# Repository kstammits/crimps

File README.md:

# crimps
 Mutated Kinks = Karltron Crimps

Originally cloning Mutable Instruments' Kinks
https://github.com/pichenettes/eurorack
Transferring from EAGLE to KiCad and updating from 0402 to 0805 construction means basically the whole thing is rewritten from scratch. The PCB is therefore unrelated to Kinks: Crimps is a karltron design 2021. 

Info on karltron.com/crimps

it's cc-by-sa so copyleft

On the internet forums, someone else has mentioned started a THT version, asking about it but not shared yet because reasons. 
https://modwiggler.com/forum/viewtopic.php?p=3644155

signal diode:
FDLL4148 is D1206

changing pinout on transistors, to SOT-23. so DO BE CAREFUL AND RECHECK THE PINOUT  (note v101 has the transistors on upside down)

layout looking fine in 0805

The S&H calls for a fancy C0G capacitor and OPA4171 opamp. We'll try it with a plain capacitor and TL074, which are compatible, but expect poor performance. I'm curious how poor, if it's acceptable we can save $$. Will try both, and report back here. But v101 is otherwise broken so 

when the input looks like noise at >9vpp, which is normal, the trigger goes off for successivly lower notes. feels like an accumulating towards -7.5Volts. Input values lower than -7V till self trigger If something softer is in the input, or values <7 volts absolute it will not self-trigger.  i think i need to add a capacitor somewhere or redo the ground plane.  Anytime the input sinks below -7V it pulls on the gate. Not sure it's really triggering, would need a two-channel scope to see if they coincide.  

if you keep the input above -7V, then the vgs doesn't trigger and everything is good. So I should just reduce the noise volume, the original kinks was showing just about +/-5V, and 10vpp is enough noise. mine's doing like 19vpp noise, and catching a very brief acquisition during noise spikes under -7V. 

so actually it works fine. i should/need/to/ reduce the noise volume to 10vpp to avoid the -7V issue. That's fixed by changing R27 from a 1.5M as originally given to a 1M. Now the noise is only +/-6V and everything works. then of course flip the transistors right-side-up. I've tested with only a J112 THT jfet tacked on crooked.  

Testing another JFET as replacement; the MMBFJ201 (marked 6P) is not great. Sort of works, sort of doesnt. The trigger time is not sufficient for acquisition, so each trigger can only move the sample by a few volts, and swinging +/-10V will need 2,3,4,5 triggers. Also, when the input is quite low the sample drains without triggers, so the J201 seems to have some leakage Igs as well as a higher Rds-on vs the J112. The incomplete-acquisitions problem might be okay for your use, but it really reduces the output range when the internal noise source is +/-6V and each trigger seems to only change the value to +/-1V. 

Testing the MMBF4392 (marked 6K)
Holds nicely down to -7.5V then drops, as others do, because my gate off voltage is -11, so less than four difference causes a sampling.   Seems to be working well. 

Testing the MMBFJ112 (marked 6R) last since a THT J112 was working well. Also seems to perform adequately. 
 
During hold testing, discovered unplugging and replugging the output causes a drop in the sample; perhaps this is caused by the brief short to ground pulling on the opamp. Additional decoupling caps did not help, looks like the OPA4171 final out buffer loses some state through the 180R output. Another output stage might be required to separate the held voltage from the output buffer. That's not fixable without additional chips.

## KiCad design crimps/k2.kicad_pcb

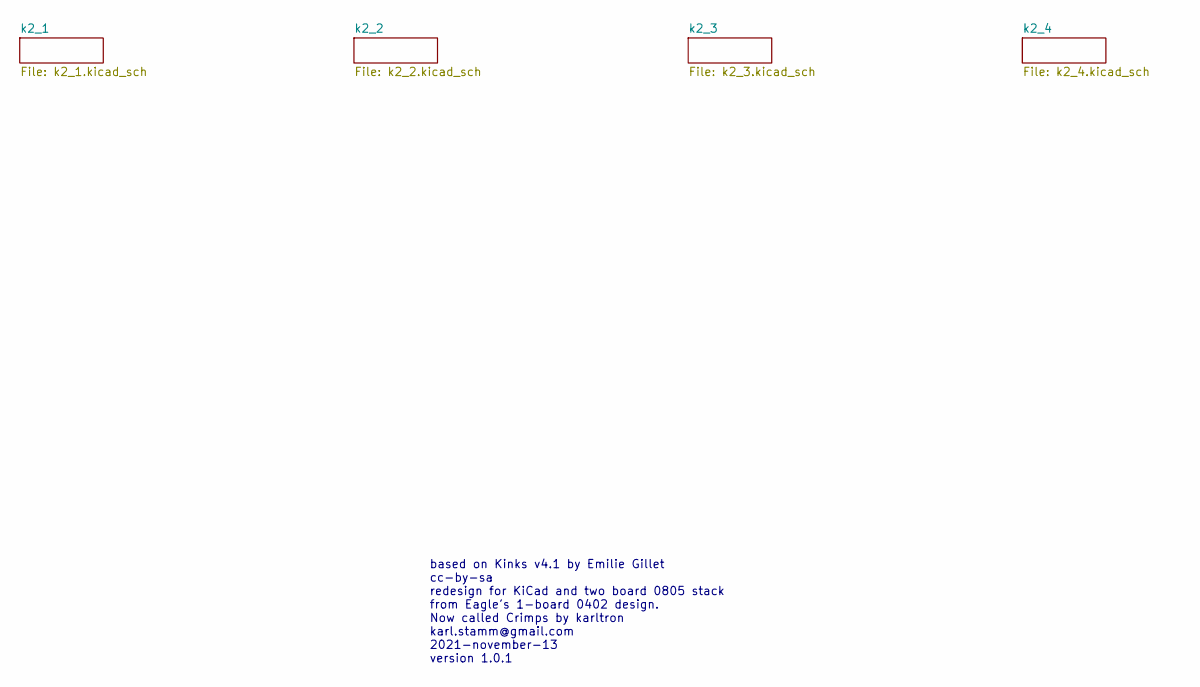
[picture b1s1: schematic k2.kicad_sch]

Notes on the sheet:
based on Kinks v4.1 by Emilie Gillet cc-by-sa redesign for KiCad and two board 0805 stack from Eagle's 1-board 0402 design. Now called Crimps by karltron karl.stamm@gmail.com 2021-november-13 version 1.0.1

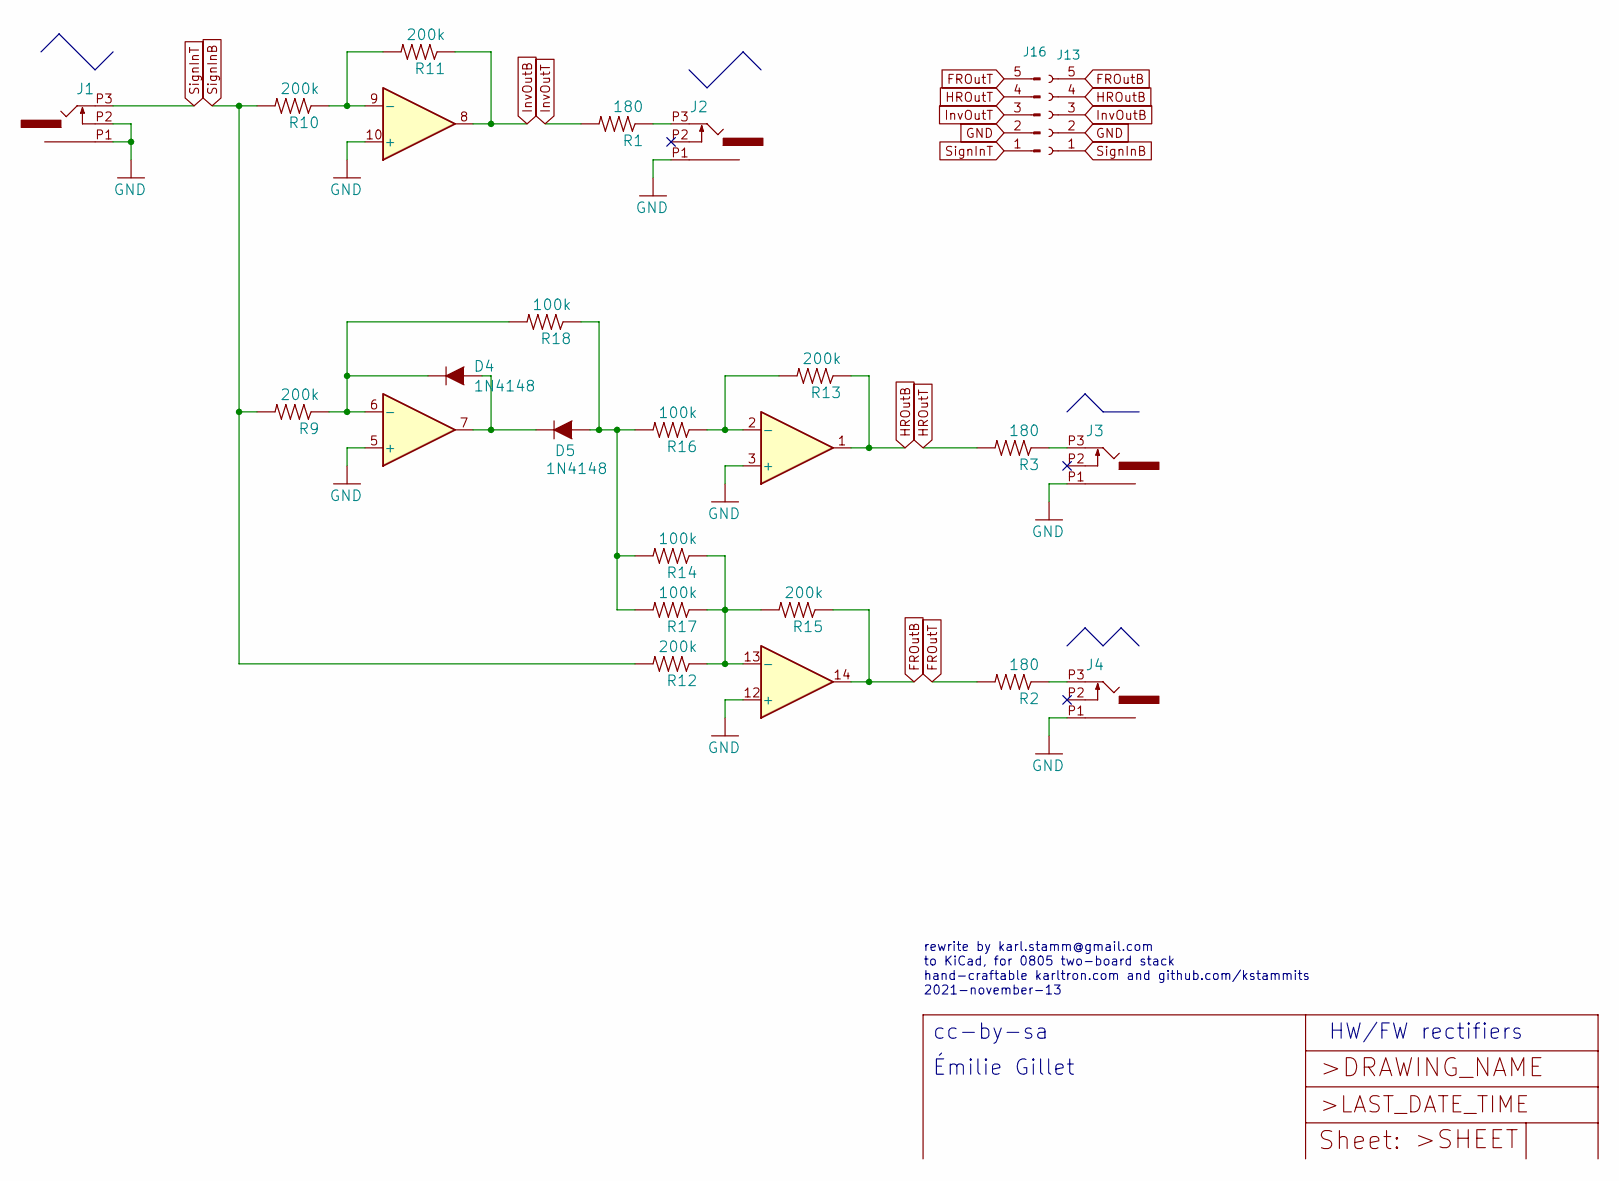
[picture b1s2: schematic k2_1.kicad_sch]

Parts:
D4, D5: 1N4148; D_1206_3216Metric_Pad1.42x1.75mm_HandSolder
IC1: TL074; SOIC-14_3.9x8.7mm_P1.27mm
J1, J2, J3, J4: PJ301_THONKICONN6; WQP_PJ_301M6
J13: Conn_01x05_Female; PinHeader_1x05_P2.54mm_Vertical
J16: Conn_01x05_Male; PinHeader_1x05_P2.54mm_Vertical
R1, R2, R3: 180; R_0805_2012Metric_Pad1.20x1.40mm_HandSolder
R9, R10, R11, R12, R13, R15: 200k; R_0805_2012Metric_Pad1.20x1.40mm_HandSolder
R14, R16, R17, R18: 100k; R_0805_2012Metric_Pad1.20x1.40mm_HandSolder

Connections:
FROutB: IC1.14, J13.5, R15.1
FROutT: J16.5, R2.2
GND: IC1.3 (+), IC1.5 (+), IC1.10 (+), IC1.12 (+), J1.P1 (1), J1.P2 (2), J2.P1 (1), J3.P1 (1), J4.P1 (1), J13.2, J16.2; also elsewhere on the board
HROutB: IC1.1, J13.4, R13.1
HROutT: J16.4, R3.2
InvOutB: IC1.8, J13.3, R11.1
InvOutT: J16.3, R1.2
unnamed: D4.2 (A), D5.1 (K), IC1.7
unnamed: D4.1 (K), IC1.6 (-), R9.1, R18.2
unnamed: D5.2 (A), R14.2, R16.2, R17.2, R18.1
unnamed: IC1.2 (-), R13.2, R16.1
unnamed: IC1.9 (-), R10.1, R11.2
unnamed: IC1.13 (-), R12.1, R14.1, R15.2, R17.1
unnamed: J2.P3 (3), R1.1
unnamed: J3.P3 (3), R3.1
unnamed: J4.P3 (3), R2.1
SignInB: J13.1, R9.2, R10.2, R12.2
SignInT: J1.P3 (3), J16.1

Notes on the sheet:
Émilie Gillet
HW/FW rectifiers
rewrite by karl.stamm@gmail.com to KiCad, for 0805 two-board stack hand-craftable karltron.com and github.com/kstammits 2021-november-13
cc-by-sa

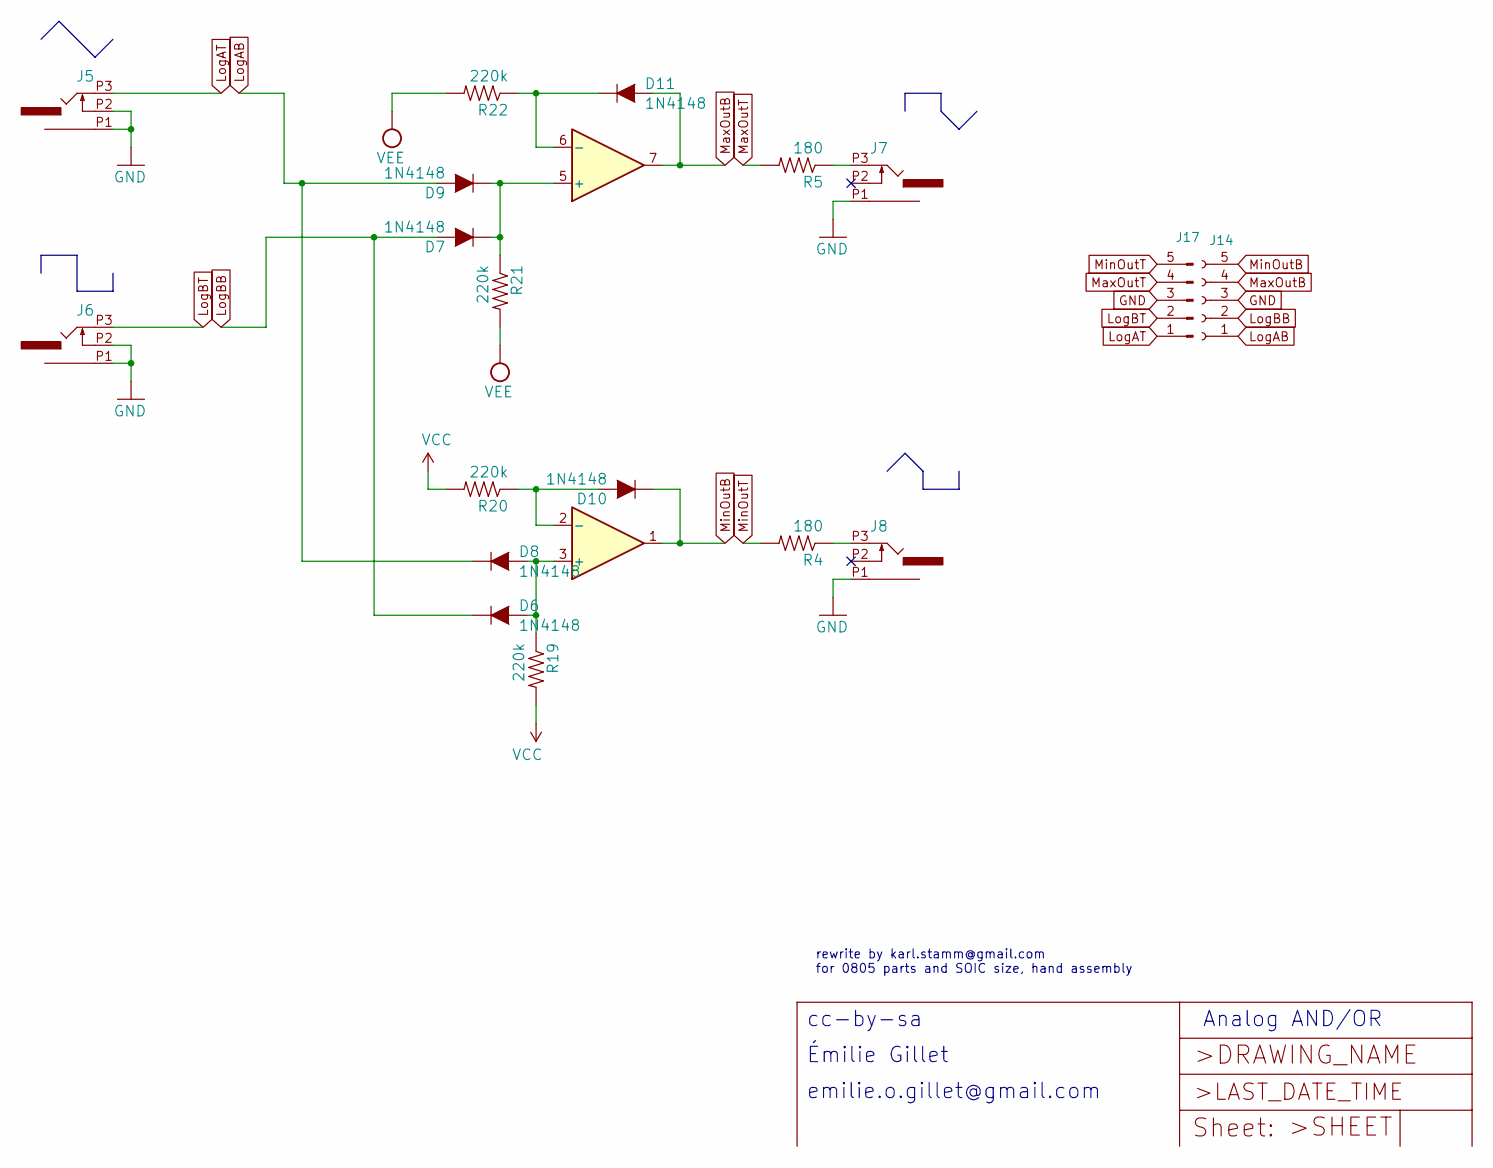
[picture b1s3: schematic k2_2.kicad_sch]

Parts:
D6, D7, D8, D9, D10, D11: 1N4148; D_1206_3216Metric_Pad1.42x1.75mm_HandSolder
IC2: TL072; SOIC-8_3.9x4.9mm_P1.27mm
J5, J6, J7, J8: PJ301_THONKICONN6; WQP_PJ_301M6
J14: Conn_01x05_Female; PinHeader_1x05_P2.54mm_Vertical
J17: Conn_01x05_Male; PinHeader_1x05_P2.54mm_Vertical
R4, R5: 180; R_0805_2012Metric_Pad1.20x1.40mm_HandSolder
R19, R20, R21, R22: 220k; R_0805_2012Metric_Pad1.20x1.40mm_HandSolder

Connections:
GND: J5.P1 (1), J5.P2 (2), J6.P1 (1), J6.P2 (2), J7.P1 (1), J8.P1 (1), J14.3, J17.3; also elsewhere on the board
LogAB: D8.1 (K), D9.2 (A), J14.1
LogAT: J5.P3 (3), J17.1
LogBB: D6.1 (K), D7.2 (A), J14.2
LogBT: J6.P3 (3), J17.2
MaxOutB: D11.2 (A), IC2.7, J14.4
MaxOutT: J17.4, R5.2
MinOutB: D10.1 (K), IC2.1, J14.5
MinOutT: J17.5, R4.2
unnamed: D6.2 (A), D8.2 (A), IC2.3 (+), R19.1
unnamed: D7.1 (K), D9.1 (K), IC2.5 (+), R21.1
unnamed: D10.2 (A), IC2.2 (-), R20.1
unnamed: D11.1 (K), IC2.6 (-), R22.1
unnamed: J7.P3 (3), R5.1
unnamed: J8.P3 (3), R4.1
VCC: R19.2, R20.2; also elsewhere on the board
VEE: R21.2, R22.2; also elsewhere on the board

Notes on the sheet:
emilie.o.gillet@gmail.com
cc-by-sa
Émilie Gillet
rewrite by karl.stamm@gmail.com for 0805 parts and SOIC size, hand assembly
Analog AND/OR

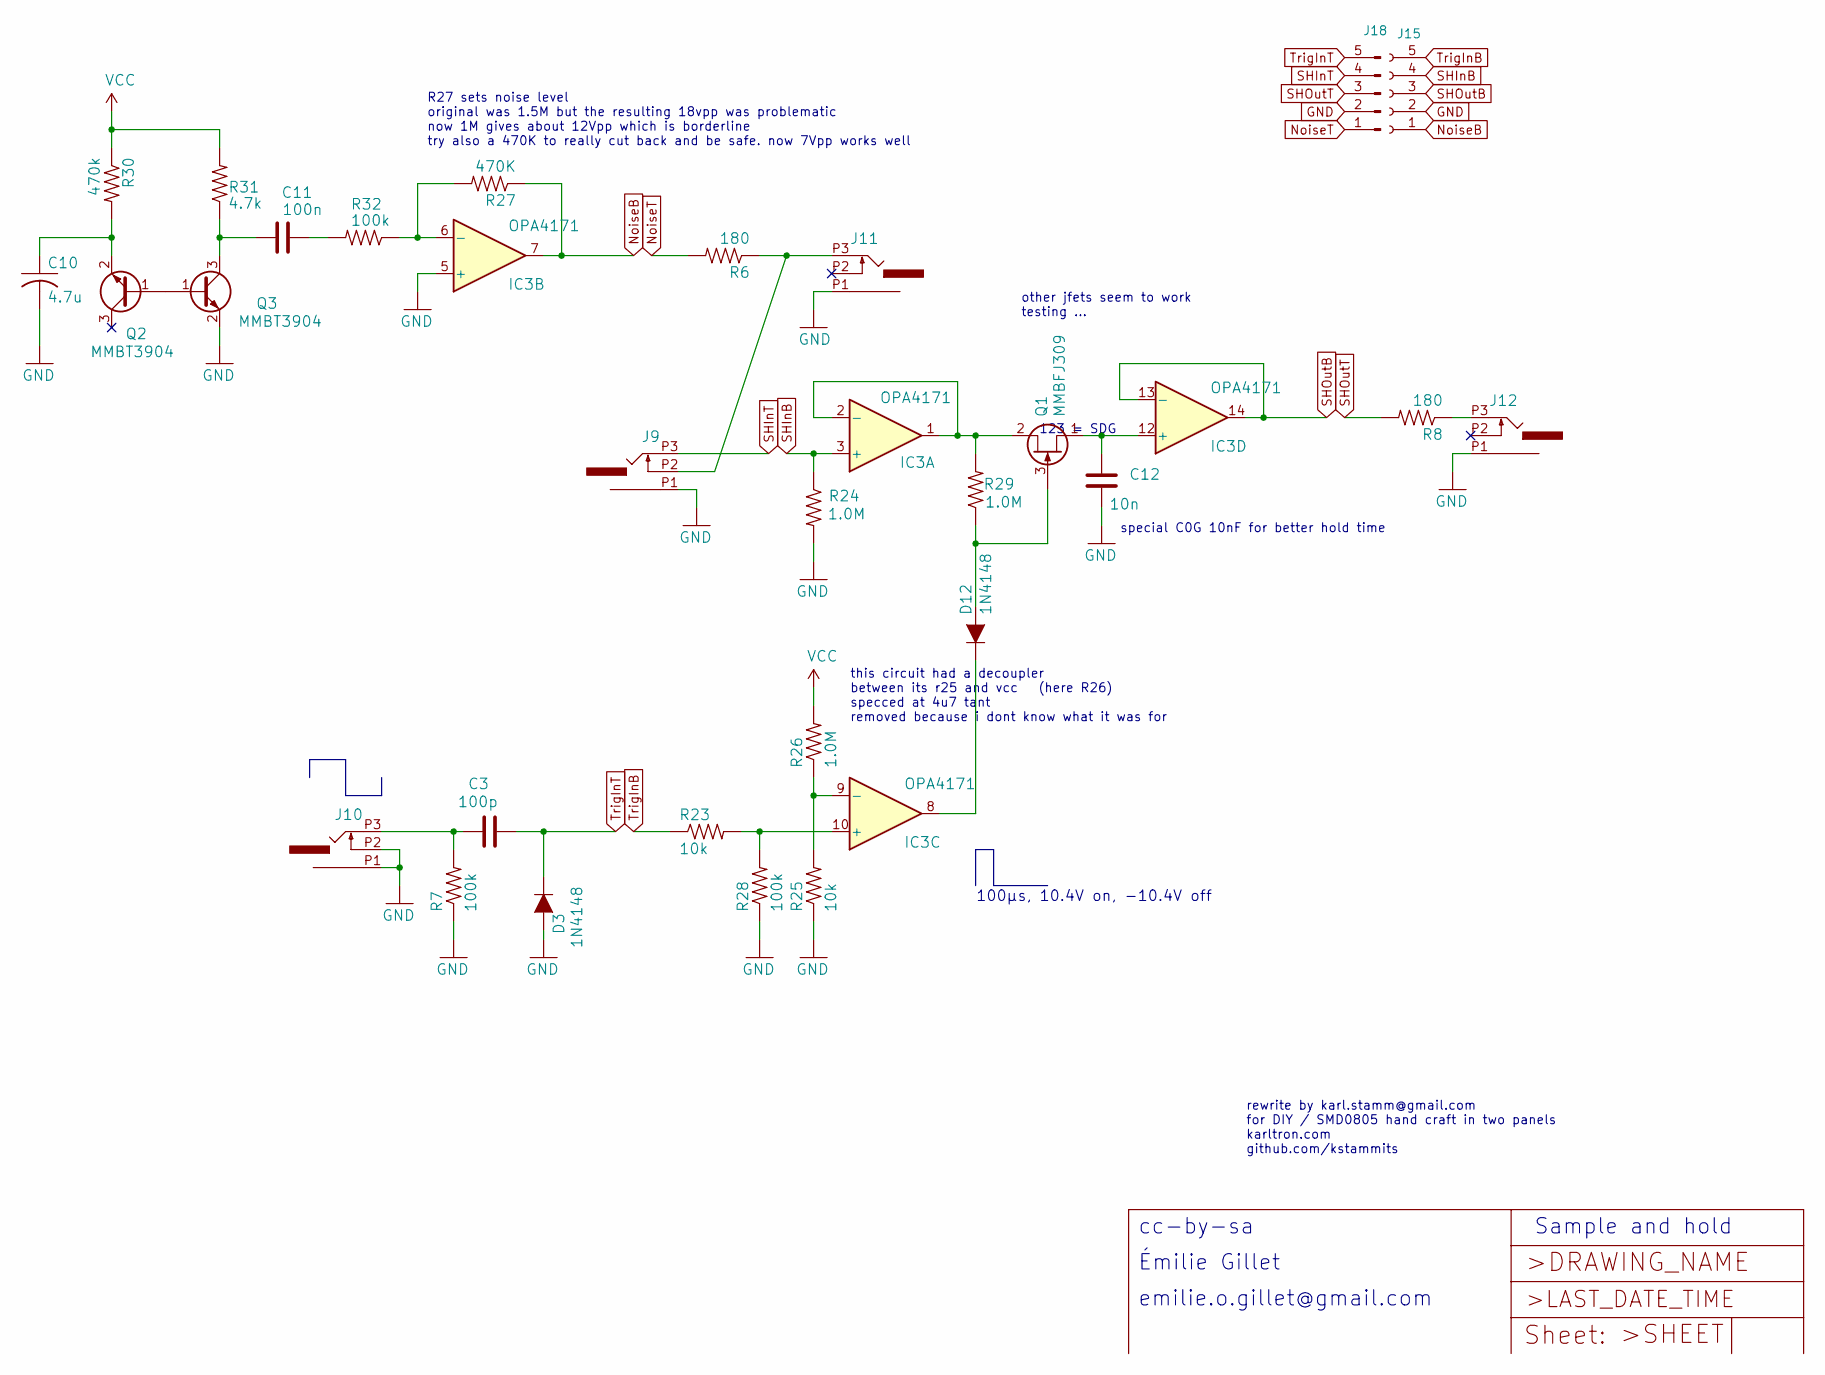
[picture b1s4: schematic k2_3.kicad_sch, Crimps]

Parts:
C3: 100p; C_0805_2012Metric_Pad1.18x1.45mm_HandSolder
C10: 4.7u; C_0805_2012Metric_Pad1.18x1.45mm_HandSolder
C11: 100n; C_0805_2012Metric_Pad1.18x1.45mm_HandSolder
C12: 10n; C_0805_2012Metric_Pad1.18x1.45mm_HandSolder
D3, D12: 1N4148; D_1206_3216Metric_Pad1.42x1.75mm_HandSolder
IC3: OPA4171; SOIC-14_3.9x8.7mm_P1.27mm
J9, J10, J11, J12: PJ301_THONKICONN6; WQP_PJ_301M6
J15: Conn_01x05_Female; PinHeader_1x05_P2.54mm_Vertical
J18: Conn_01x05_Male; PinHeader_1x05_P2.54mm_Vertical
Q1: MMBFJ309; SOT-23_Handsoldering
Q2, Q3: MMBT3904; SOT-23_Handsoldering
R6, R8: 180; R_0805_2012Metric_Pad1.20x1.40mm_HandSolder
R7, R28, R32: 100k; R_0805_2012Metric_Pad1.20x1.40mm_HandSolder
R23, R25: 10k; R_0805_2012Metric_Pad1.20x1.40mm_HandSolder
R24, R26, R29: 1.0M; R_0805_2012Metric_Pad1.20x1.40mm_HandSolder
R27: 470K; R_0805_2012Metric_Pad1.20x1.40mm_HandSolder
R30: 470k; R_0805_2012Metric_Pad1.20x1.40mm_HandSolder
R31: 4.7k; R_0805_2012Metric_Pad1.20x1.40mm_HandSolder

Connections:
GND: C10.2, C12.2, D3.2 (A), IC3.5 (+), J9.P1 (1), J10.P1 (1), J10.P2 (2), J11.P1 (1), J12.P1 (1), J15.2, J18.2, Q3.2 (E), R7.1, R24.2, R25.1, R28.1; also elsewhere on the board
unnamed: C11.2, R32.2
unnamed: D12.2 (A), Q1.3 (G), R29.1
unnamed: D12.1 (K), IC3.8
unnamed: IC3.1, IC3.2 (-), Q1.2 (D), R29.2
unnamed: IC3.6 (-), R27.2, R32.1
unnamed: IC3.10 (+), R23.2, R28.2
unnamed: IC3.9 (-), R25.2, R26.1
unnamed: C12.1, IC3.12 (+), Q1.1 (S)
unnamed: C3.1, J10.P3 (3), R7.2
unnamed: J9.P2 (2), J11.P3 (3), R6.1
unnamed: J12.P3 (3), R8.1
unnamed: Q2.1 (B), Q3.1 (B)
unnamed: C10.1, Q2.2 (E), R30.2
unnamed: C11.1, Q3.3 (C), R31.1
NoiseB: IC3.7, J15.1, R27.1
NoiseT: J18.1, R6.2
SHInB: IC3.3 (+), J15.4, R24.1
SHInT: J9.P3 (3), J18.4
SHOutB: IC3.13 (-), IC3.14, J15.3
SHOutT: J18.3, R8.2
TrigInB: J15.5, R23.1
TrigInT: C3.2, D3.1 (K), J18.5
VCC: R26.2, R30.1, R31.2; also elsewhere on the board

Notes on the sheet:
special C0G 10nF for better hold time
rewrite by karl.stamm@gmail.com for DIY / SMD0805 hand craft in two panels karltron.com github.com/kstammits
cc-by-sa
100µs, 10.4V on, -10.4V off
this circuit had a decoupler between its r25 and vcc (here R26) specced at 4u7 tant removed because i dont know what it was for
Émilie Gillet
123 = SDG
emilie.o.gillet@gmail.com
R27 sets noise level original was 1.5M but the resulting 18vpp was problematic now 1M gives about 12Vpp which is borderline try also a 470K to really cut back and be safe. now 7Vpp works well
Sample and hold
other jfets seem to work testing ...

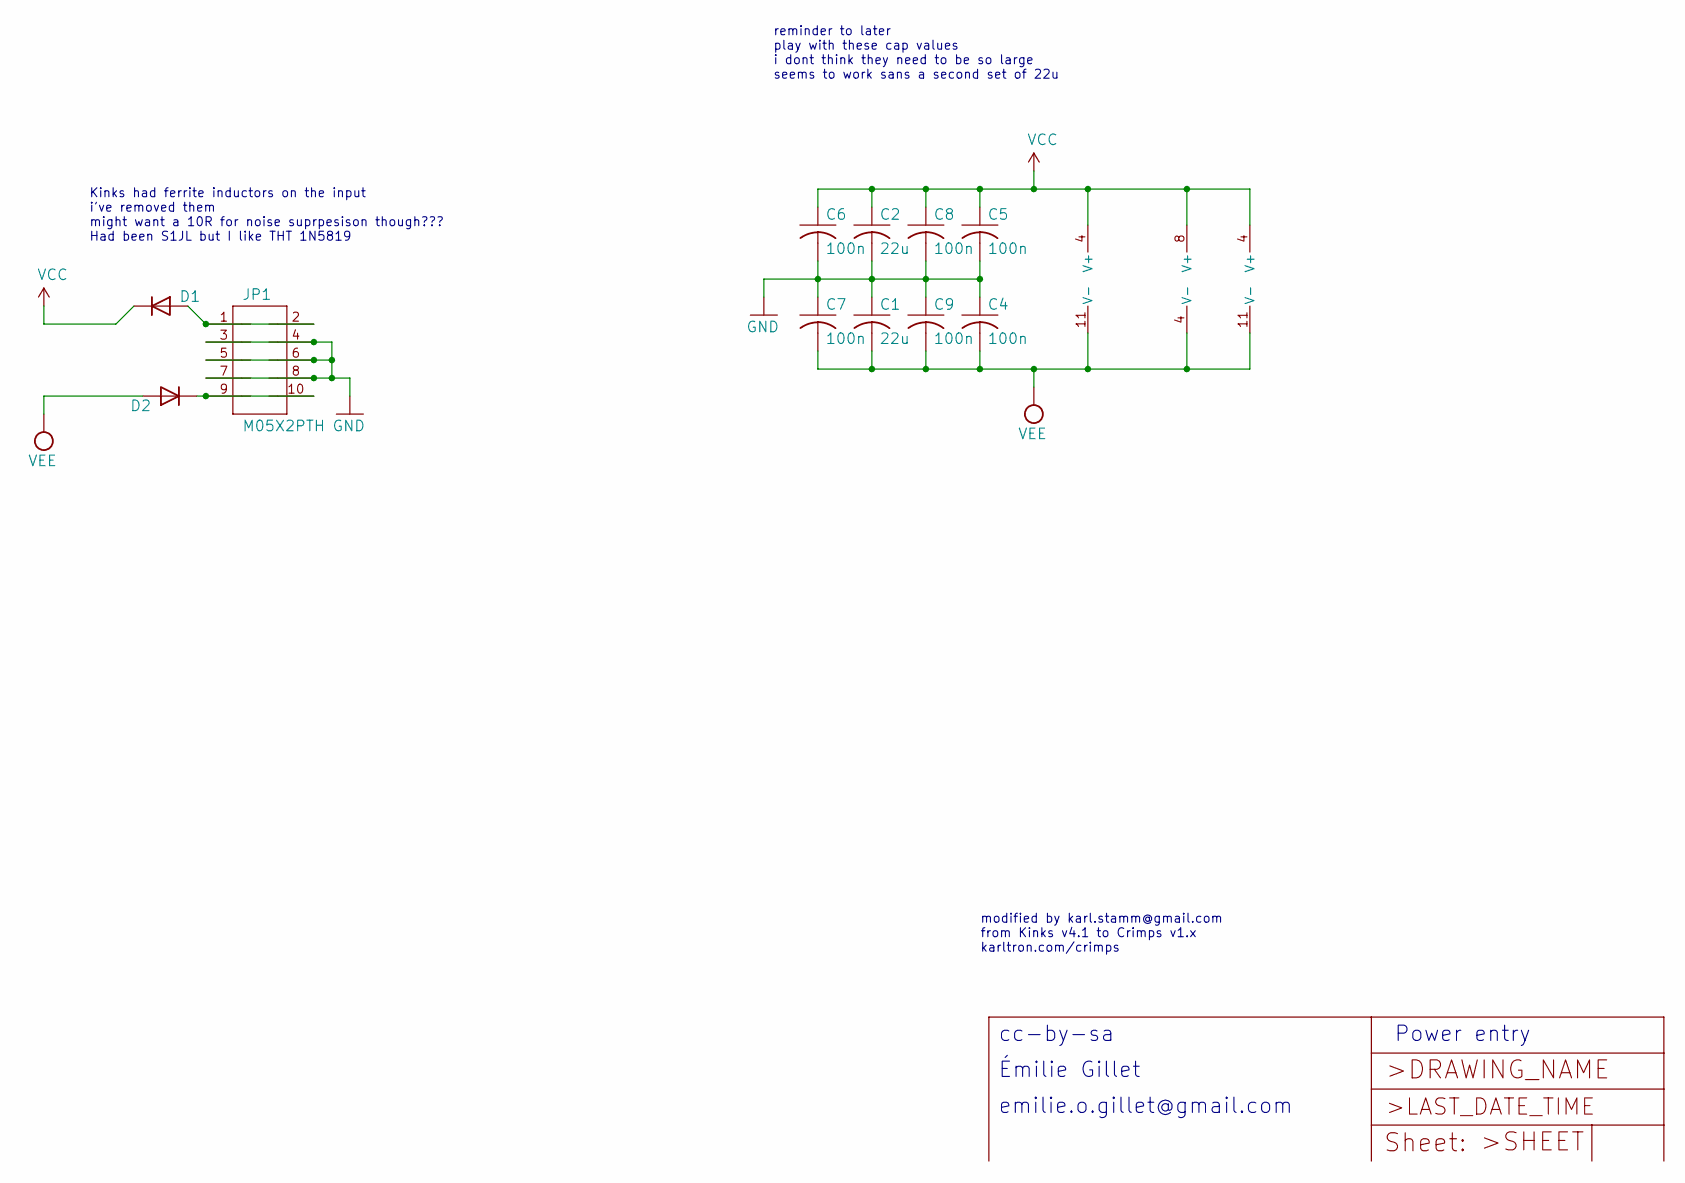
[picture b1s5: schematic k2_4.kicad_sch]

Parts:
C1, C2: 22u; CP_Radial_D6.3mm_P2.50mm
C4, C5, C6, C7, C8, C9: 100n; C_0805_2012Metric_Pad1.18x1.45mm_HandSolder
D1, D2: S1JL; D_DO-41_SOD81_P10.16mm_Horizontal
IC1: TL074; SOIC-14_3.9x8.7mm_P1.27mm
IC2: TL072; SOIC-8_3.9x4.9mm_P1.27mm
IC3: OPA4171; SOIC-14_3.9x8.7mm_P1.27mm
JP1: M05X2PTH; AVR_ICSP

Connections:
GND: C1.1, C2.2, C4.1, C5.2, C6.2, C7.1, C8.2, C9.1, JP1.3, JP1.4, JP1.5, JP1.6, JP1.7, JP1.8; also elsewhere on the board
unnamed: D1.2 (A), JP1.1, JP1.2
unnamed: D2.1 (K), JP1.9, JP1.10
VCC: C2.1, C5.1, C6.1, C8.1, D1.1 (K), IC1.4 (V+), IC2.8 (V+), IC3.4 (V+); also elsewhere on the board
VEE: C1.2, C4.2, C7.2, C9.2, D2.2 (A), IC1.11 (V-), IC2.4 (V-), IC3.11 (V-); also elsewhere on the board

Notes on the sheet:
Émilie Gillet
Kinks had ferrite inductors on the input i've removed them might want a 10R for noise suprpesison though??? Had been S1JL but I like THT 1N5819
Power entry
cc-by-sa
reminder to later play with these cap values i dont think they need to be so large seems to work sans a second set of 22u
modified by karl.stamm@gmail.com from Kinks v4.1 to Crimps v1.x karltron.com/crimps
emilie.o.gillet@gmail.com

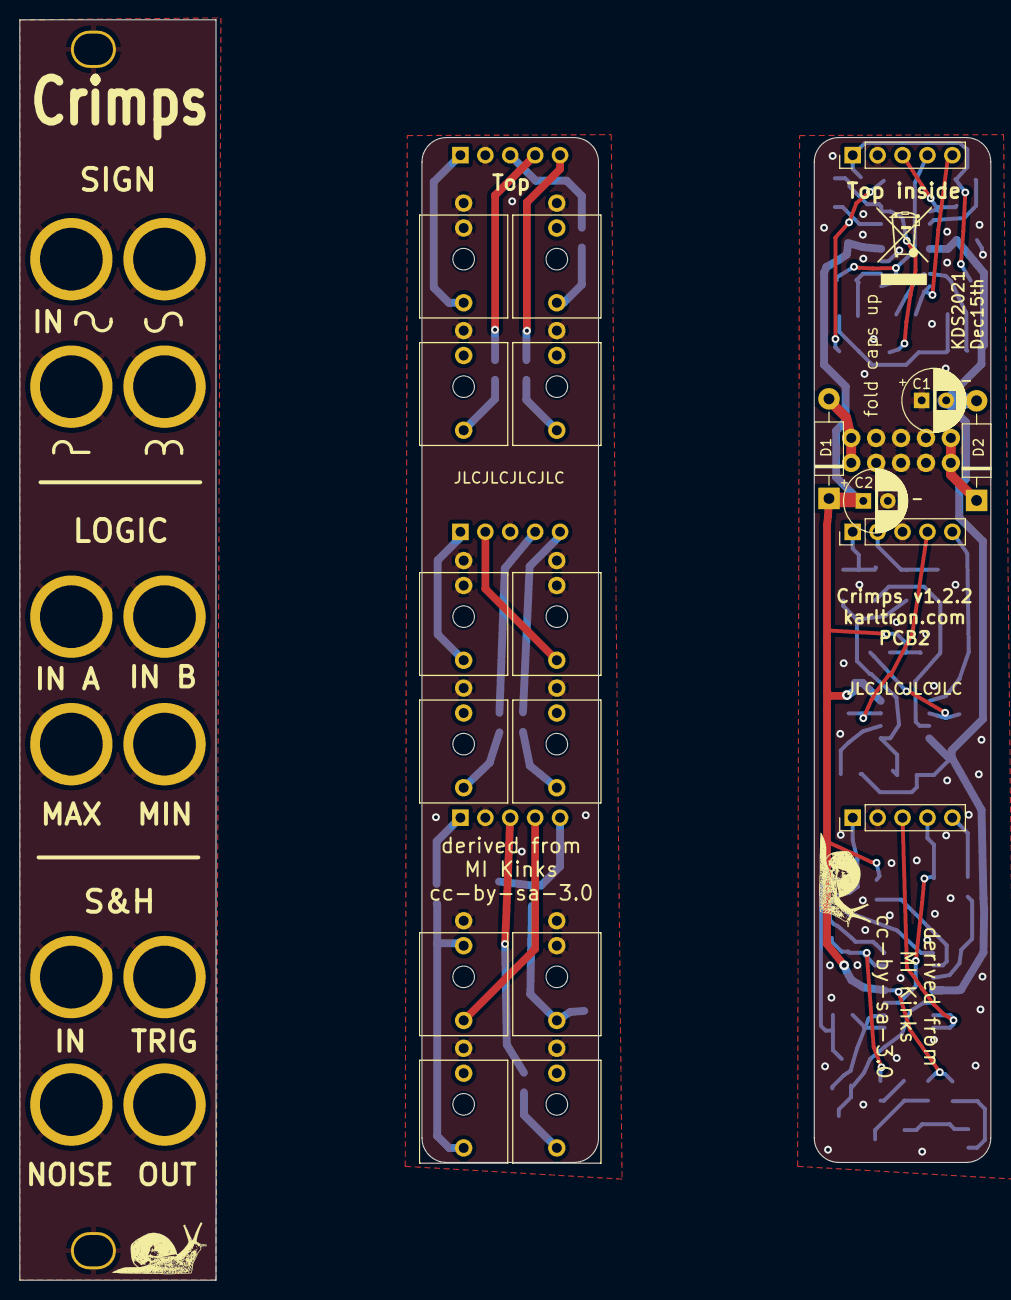
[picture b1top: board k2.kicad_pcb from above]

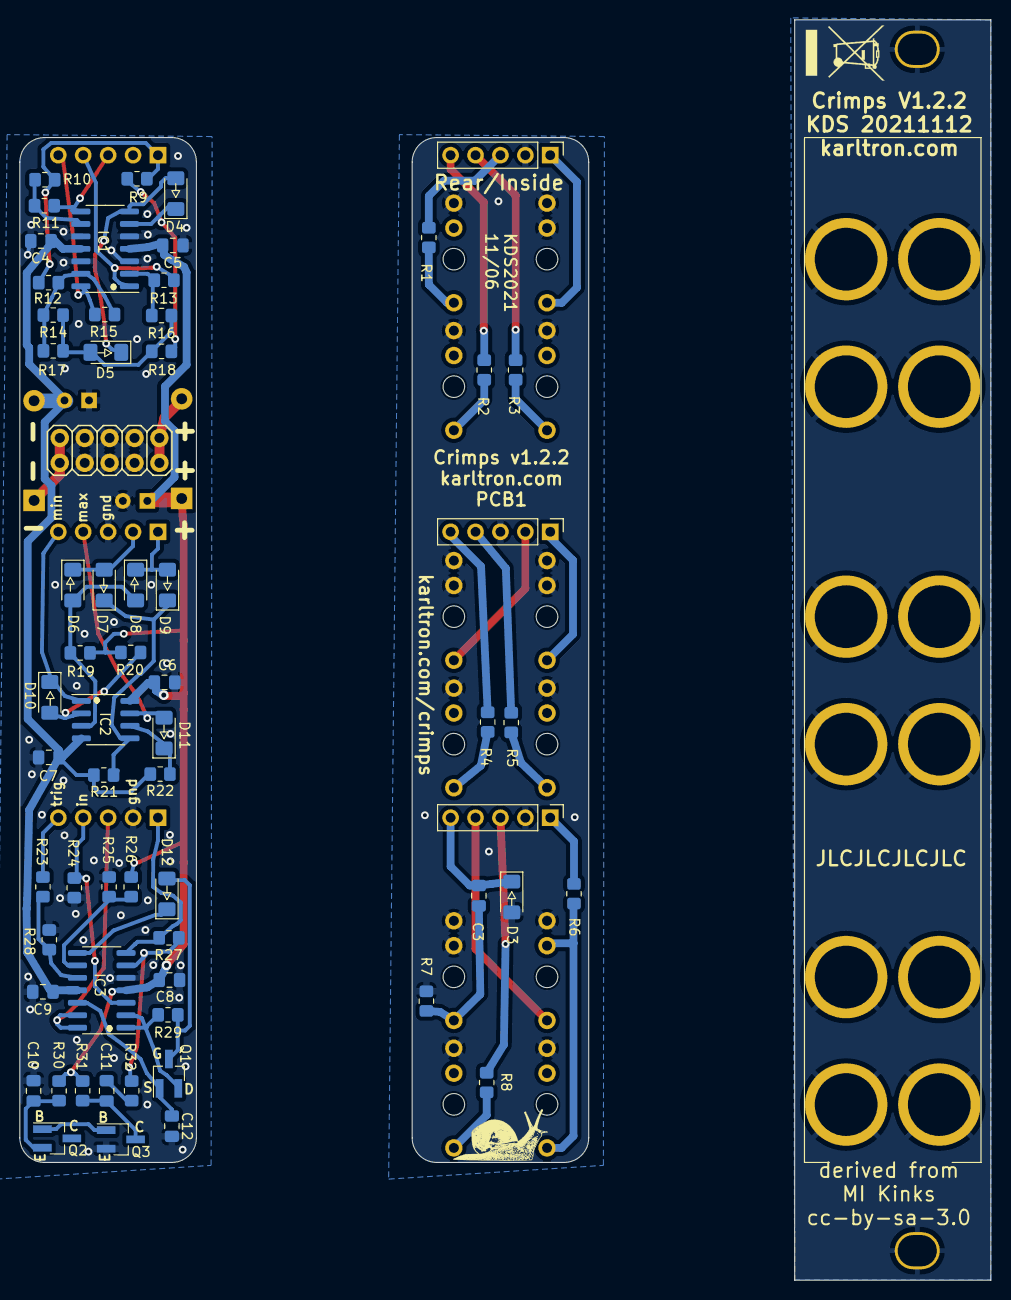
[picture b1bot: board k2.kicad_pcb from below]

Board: 2 copper layers, 99.0 x 128.5 mm, 96 parts (62 on the bottom side), 58 nets.

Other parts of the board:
G1: Logo_Open_Hardware_Small; snail4.sm
H1, H14: MountingHole_Pad; SLOT-1
H2, H2#2, H2#3, H2#4, H2#5, H2#6, H2#7, H2#8, H2#9: J1; MountingHole_6.4mm_M6_Pad
H6, H6#2, H6#3: J2; MountingHole_6.4mm_M6_Pad

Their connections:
GND: H1.1, H2.1, H2#2.1, H2#3.1, H2#4.1, H2#5.1, H2#6.1, H2#7.1, H2#8.1, H2#9.1, H6.1, H6#2.1, H6#3.1, H14.1; also elsewhere on the board

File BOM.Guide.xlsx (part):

Source: | /Users/karl/Workspace/KiCad/Crimps/crimps/k2.sch
Date: | Thursday, November 18, 2021 at 08:59:49 PM
Tool: | Eeschema (5.1.10-1-10_14)
Generator: | /private/var/folders/6g/062y2qc95n76y3fy2wkwz5l40000gn/T/AppTranslocation/AF1E8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
Component Count: | 81
Individual Components:
Item | Qty | Reference(s) | Value | LibPart | Footprint | Datasheet
 |  | C1 | 22u | k2-eagle-import:C-USC0805 | Capacitor_THT:CP_Radial_D6.3mm_P2.50mm
 |  | C2 | 22u | k2-eagle-import:C-USC0805 | Capacitor_THT:CP_Radial_D6.3mm_P2.50mm
 |  | C3 | 100p | device:C | Capacitor_SMD:C_0805_2012Metric_Pad1.18x1.45mm_HandSolder
 |  | C4 | 100n | k2-eagle-import:C-USC0402 | Capacitor_SMD:C_0805_2012Metric_Pad1.18x1.45mm_HandSolder
 |  | C5 | 100n | k2-eagle-import:C-USC0402 | Capacitor_SMD:C_0805_2012Metric_Pad1.18x1.45mm_HandSolder
 |  | C6 | 100n | k2-eagle-import:C-USC0805 | Capacitor_SMD:C_0805_2012Metric_Pad1.18x1.45mm_HandSolder
 |  | C7 | 100n | k2-eagle-import:C-USC0805 | Capacitor_SMD:C_0805_2012Metric_Pad1.18x1.45mm_HandSolder
 |  | C8 | 100n | k2-eagle-import:C-USC0402 | Capacitor_SMD:C_0805_2012Metric_Pad1.18x1.45mm_HandSolder
 |  | C9 | 100n | k2-eagle-import:C-USC0402 | Capacitor_SMD:C_0805_2012Metric_Pad1.18x1.45mm_HandSolder
 |  | C10 | 4.7u | k2-eagle-import:C-USC0603 | Capacitor_SMD:C_0805_2012Metric_Pad1.18x1.45mm_HandSolder
 |  | C11 | 100n | device:C | Capacitor_SMD:C_0805_2012Metric_Pad1.18x1.45mm_HandSolder
 |  | C12 | 10n | device:C | Capacitor_SMD:C_0805_2012Metric_Pad1.18x1.45mm_HandSolder
 |  | D1 | S1JL | Device:D | Diode_THT:D_DO-41_SOD81_P10.16mm_Horizontal
 |  | D2 | S1JL | Device:D | Diode_THT:D_DO-41_SOD81_P10.16mm_Horizontal
 |  | D3 | 1N4148 | device:D | Diode_SMD:D_1206_3216Metric_Pad1.42x1.75mm_HandSolder
 |  | D4 | 1N4148 | device:D | Diode_SMD:D_1206_3216Metric_Pad1.42x1.75mm_HandSolder
 |  | D5 | 1N4148 | device:D | Diode_SMD:D_1206_3216Metric_Pad1.42x1.75mm_HandSolder
 |  | D6 | 1N4148 | device:D | Diode_SMD:D_1206_3216Metric_Pad1.42x1.75mm_HandSolder
 |  | D7 | 1N4148 | device:D | Diode_SMD:D_1206_3216Metric_Pad1.42x1.75mm_HandSolder
 |  | D8 | 1N4148 | device:D | Diode_SMD:D_1206_3216Metric_Pad1.42x1.75mm_HandSolder
 |  | D9 | 1N4148 | device:D | Diode_SMD:D_1206_3216Metric_Pad1.42x1.75mm_HandSolder
 |  | D10 | 1N4148 | device:D | Diode_SMD:D_1206_3216Metric_Pad1.42x1.75mm_HandSolder
 |  | D11 | 1N4148 | device:D | Diode_SMD:D_1206_3216Metric_Pad1.42x1.75mm_HandSolder
 |  | D12 | 1N4148 | device:D | Diode_SMD:D_1206_3216Metric_Pad1.42x1.75mm_HandSolder
 |  | IC1 | TL074 | Amplifier_Operational:TL074 | Package_SO:SOIC-14_3.9x8.7mm_P1.27mm
 |  | IC2 | TL072 | Amplifier_Operational:TL072 | Package_SO:SOIC-8_3.9x4.9mm_P1.27mm
 |  | IC3 | TL074 | Amplifier_Operational:TL074 | Package_SO:SOIC-14_3.9x8.7mm_P1.27mm
 |  | J1 | PJ301_THONKICONN6 | k2-eagle-import:PJ301_THONKICONN6 | k2:WQP_PJ_301M6
 |  | J2 | PJ301_THONKICONN6 | k2-eagle-import:PJ301_THONKICONN6 | k2:WQP_PJ_301M6
 |  | J3 | PJ301_THONKICONN6 | k2-eagle-import:PJ301_THONKICONN6 | k2:WQP_PJ_301M6
 |  | J4 | PJ301_THONKICONN6 | k2-eagle-import:PJ301_THONKICONN6 | k2:WQP_PJ_301M6
 |  | J5 | PJ301_THONKICONN6 | k2-eagle-import:PJ301_THONKICONN6 | k2:WQP_PJ_301M6
 |  | J6 | PJ301_THONKICONN6 | k2-eagle-import:PJ301_THONKICONN6 | k2:WQP_PJ_301M6
 |  | J7 | PJ301_THONKICONN6 | k2-eagle-import:PJ301_THONKICONN6 | k2:WQP_PJ_301M6
 |  | J8 | PJ301_THONKICONN6 | k2-eagle-import:PJ301_THONKICONN6 | k2:WQP_PJ_301M6
 |  | J9 | PJ301_THONKICONN6 | k2-eagle-import:PJ301_THONKICONN6 | k2:WQP_PJ_301M6
 |  | J10 | PJ301_THONKICONN6 | k2-eagle-import:PJ301_THONKICONN6 | k2:WQP_PJ_301M6
 |  | J11 | PJ301_THONKICONN6 | k2-eagle-import:PJ301_THONKICONN6 | k2:WQP_PJ_301M6
 |  | J12 | PJ301_THONKICONN6 | k2-eagle-import:PJ301_THONKICONN6 | k2:WQP_PJ_301M6
 |  | J13 | Conn_01x05_Female | Connector:Conn_01x05_Female | Connector_PinHeader_2.54mm:PinHeader_1x05_P2.54mm_Vertical | ~
 |  | J14 | Conn_01x05_Female | Connector:Conn_01x05_Female | Connector_PinHeader_2.54mm:PinHeader_1x05_P2.54mm_Vertical | ~
 |  | J15 | Conn_01x05_Female | Connector:Conn_01x05_Female | Connector_PinHeader_2.54mm:PinHeader_1x05_P2.54mm_Vertical | ~
 |  | J16 | Conn_01x05_Male | Connector:Conn_01x05_Male | Connector_PinHeader_2.54mm:PinHeader_1x05_P2.54mm_Vertical | ~
 |  | J17 | Conn_01x05_Male | Connector:Conn_01x05_Male | Connector_PinHeader_2.54mm:PinHeader_1x05_P2.54mm_Vertical | ~
 |  | J18 | Conn_01x05_Male | Connector:Conn_01x05_Male | Connector_PinHeader_2.54mm:PinHeader_1x05_P2.54mm_Vertical | ~
 |  | JP1 | M05X2PTH | k2-eagle-import:M05X2PTH | k2:AVR_ICSP
 |  | Q1 | MMBFJ309 | device:Q_NJFET_SDG | Package_TO_SOT_SMD:SOT-23_Handsoldering
 |  | Q2 | MMBT3904 | device:Q_NPN_EBC | Package_TO_SOT_SMD:SOT-23_Handsoldering
 |  | Q3 | MMBT3904 | device:Q_NPN_EBC | Package_TO_SOT_SMD:SOT-23_Handsoldering
 |  | R1 | 180 | k2-eagle-import:R-US_R0402 | Resistor_SMD:R_0805_2012Metric_Pad1.20x1.40mm_HandSolder
 |  | R2 | 180 | k2-eagle-import:R-US_R0402 | Resistor_SMD:R_0805_2012Metric_Pad1.20x1.40mm_HandSolder
 |  | R3 | 180 | k2-eagle-import:R-US_R0402 | Resistor_SMD:R_0805_2012Metric_Pad1.20x1.40mm_HandSolder
 |  | R4 | 180 | k2-eagle-import:R-US_R0402 | Resistor_SMD:R_0805_2012Metric_Pad1.20x1.40mm_HandSolder
 |  | R5 | 180 | k2-eagle-import:R-US_R0402 | Resistor_SMD:R_0805_2012Metric_Pad1.20x1.40mm_HandSolder
 |  | R6 | 180 | k2-eagle-import:R-US_R0402 | Resistor_SMD:R_0805_2012Metric_Pad1.20x1.40mm_HandSolder
 |  | R7 | 100k | k2-eagle-import:R-US_R0402 | Resistor_SMD:R_0805_2012Metric_Pad1.20x1.40mm_HandSolder
 |  | R8 | 180 | k2-eagle-import:R-US_R0402 | Resistor_SMD:R_0805_2012Metric_Pad1.20x1.40mm_HandSolder
 |  | R9 | 200k | k2-eagle-import:R-US_R0402 | Resistor_SMD:R_0805_2012Metric_Pad1.20x1.40mm_HandSolder
 |  | R10 | 200k | k2-eagle-import:R-US_R0402 | Resistor_SMD:R_0805_2012Metric_Pad1.20x1.40mm_HandSolder
 |  | R11 | 200k | k2-eagle-import:R-US_R0402 | Resistor_SMD:R_0805_2012Metric_Pad1.20x1.40mm_HandSolder
 |  | R12 | 200k | k2-eagle-import:R-US_R0402 | Resistor_SMD:R_0805_2012Metric_Pad1.20x1.40mm_HandSolder
 |  | R13 | 200k | k2-eagle-import:R-US_R0402 | Resistor_SMD:R_0805_2012Metric_Pad1.20x1.40mm_HandSolder
 |  | R14 | 100k | k2-eagle-import:R-US_R0402 | Resistor_SMD:R_0805_2012Metric_Pad1.20x1.40mm_HandSolder
 |  | R15 | 200k | k2-eagle-import:R-US_R0402 | Resistor_SMD:R_0805_2012Metric_Pad1.20x1.40mm_HandSolder
 |  | R16 | 100k | k2-eagle-import:R-US_R0402 | Resistor_SMD:R_0805_2012Metric_Pad1.20x1.40mm_HandSolder
 |  | R17 | 100k | k2-eagle-import:R-US_R0402 | Resistor_SMD:R_0805_2012Metric_Pad1.20x1.40mm_HandSolder
 |  | R18 | 100k | k2-eagle-import:R-US_R0402 | Resistor_SMD:R_0805_2012Metric_Pad1.20x1.40mm_HandSolder
 |  | R19 | 220k | k2-eagle-import:R-US_R0402 | Resistor_SMD:R_0805_2012Metric_Pad1.20x1.40mm_HandSolder
 |  | R20 | 220k | k2-eagle-import:R-US_R0402 | Resistor_SMD:R_0805_2012Metric_Pad1.20x1.40mm_HandSolder
 |  | R21 | 220k | k2-eagle-import:R-US_R0402 | Resistor_SMD:R_0805_2012Metric_Pad1.20x1.40mm_HandSolder
 |  | R22 | 220k | k2-eagle-import:R-US_R0402 | Resistor_SMD:R_0805_2012Metric_Pad1.20x1.40mm_HandSolder
 |  | R23 | 10k | k2-eagle-import:R-US_R0402 | Resistor_SMD:R_0805_2012Metric_Pad1.20x1.40mm_HandSolder
 |  | R24 | 1.0M | k2-eagle-import:R-US_R0402 | Resistor_SMD:R_0805_2012Metric_Pad1.20x1.40mm_HandSolder
 |  | R25 | 10k | k2-eagle-import:R-US_R0402 | Resistor_SMD:R_0805_2012Metric_Pad1.20x1.40mm_HandSolder
 |  | R26 | 1.0M | k2-eagle-import:R-US_R0402 | Resistor_SMD:R_0805_2012Metric_Pad1.20x1.40mm_HandSolder
 |  | R27 | 1.5M | k2-eagle-import:R-US_R0402 | Resistor_SMD:R_0805_2012Metric_Pad1.20x1.40mm_HandSolder
 |  | R28 | 100k | k2-eagle-import:R-US_R0402 | Resistor_SMD:R_0805_2012Metric_Pad1.20x1.40mm_HandSolder
 |  | R29 | 1.0M | k2-eagle-import:R-US_R0402 | Resistor_SMD:R_0805_2012Metric_Pad1.20x1.40mm_HandSolder
 |  | R30 | 470k | k2-eagle-import:R-US_R0402 | Resistor_SMD:R_0805_2012Metric_Pad1.20x1.40mm_HandSolder
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

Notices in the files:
Jinx/Jinx.kicad_pcb:
cc-by-sa-3.0
